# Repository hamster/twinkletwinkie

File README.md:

#TwinkleTwinkie SAO

For fun, I made a twinkling twinkie SAO for my friend @mrtwinkletwink for defcon27.

It is based on an attiny1616, has 3 LEDs and one big capacitive touch button.

 - PDF version is [here](twinkletwinkie.pdf)

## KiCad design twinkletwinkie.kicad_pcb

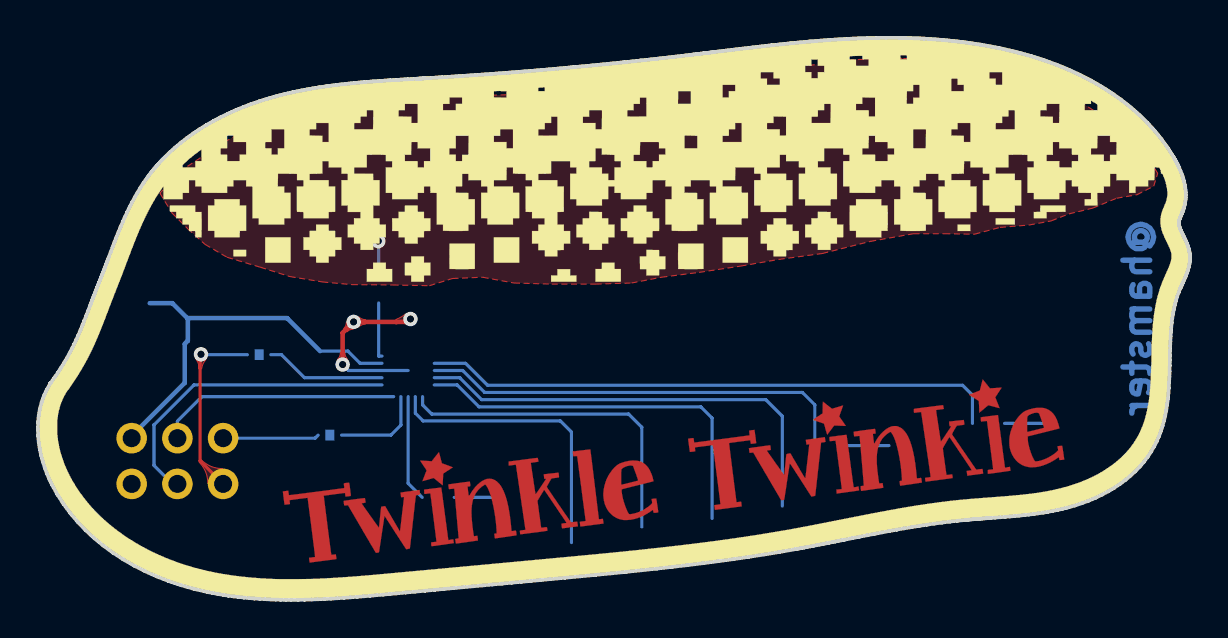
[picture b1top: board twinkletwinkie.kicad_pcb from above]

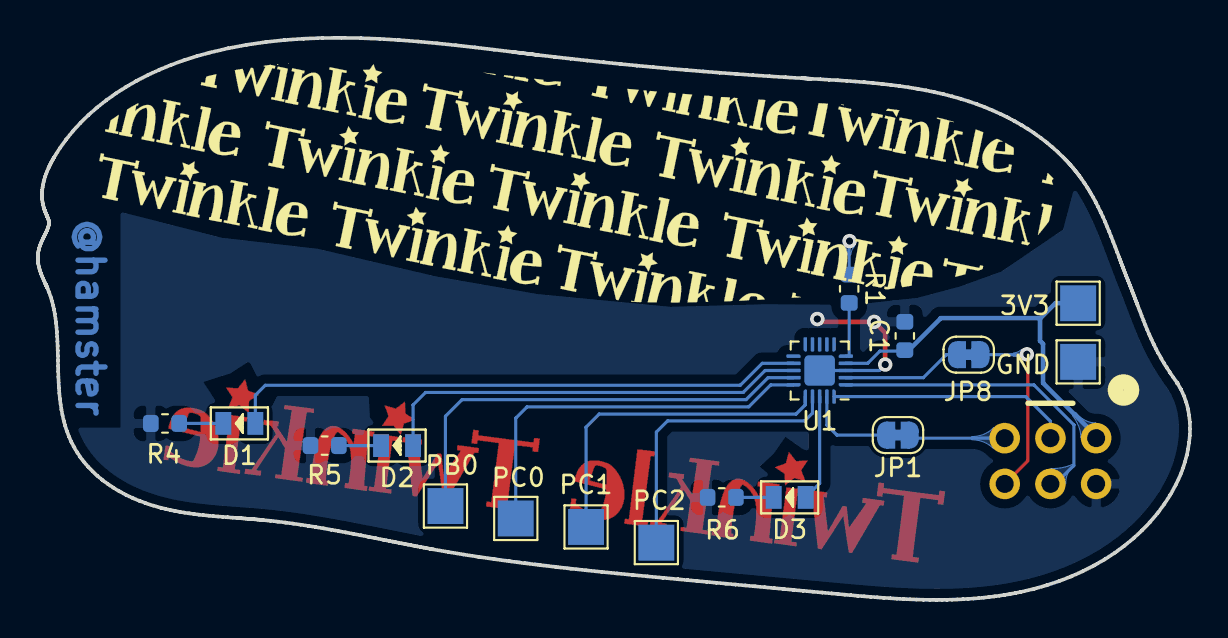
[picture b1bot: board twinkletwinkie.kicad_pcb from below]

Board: 2 copper layers, 64.0 x 31.2 mm, 18 parts (17 on the bottom side), 19 nets.

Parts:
3V3: PB2; TestPoint_Pad_2.0x2.0mm
C1: C; C_0603_1608Metric
D1, D2, D3: LED; LED-0805
GND: PB3; TestPoint_Pad_2.0x2.0mm
JP1, JP8: SolderJumper_2_Bridged; SolderJumper-2_P1.3mm_Bridged_RoundedPad1.0x1.5mm
PB0: PB0; TestPoint_Pad_2.0x2.0mm
PC0: PC0; TestPoint_Pad_2.0x2.0mm
PC1: PC1; TestPoint_Pad_2.0x2.0mm
PC2: PC2; TestPoint_Pad_2.0x2.0mm
R1: 1k; R_0603_1608Metric
R4, R5, R6: 33R; R_0603_1608Metric
U1: ATtiny816-M; VQFN-20-1EP_3x3mm_P0.4mm_EP1.7x1.7mm
X1: Badgelife_sao_connector_v169bis; Badgelife-Shitty-v1.69bis

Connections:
+3V3: 3V3.1, C1.1, U1.4, X1.1
GND: C1.2, GND.1, R4.1, R5.1, R6.1, U1.3, U1.21, X1.2
unnamed: D1.1, R4.2
unnamed: D2.1, R5.2
unnamed: D3.1, R6.2
unnamed: JP1.1, X1.5
unnamed: JP8.2, X1.6
PA0: JP1.2, U1.19
PA1: U1.20, X1.3
PA2: U1.1, X1.4
PA3: JP8.1, U1.2
PA4: R1.2, U1.5
PB0: PB0.1, U1.14
PB1: D2.2, U1.13
PB2: D1.2, U1.12
PC0: PC0.1, U1.15
PC1: PC1.1, U1.16
PC2: PC2.1, U1.17
PC3: D3.2, U1.18

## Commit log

2019-08-23 Adding design files for the TwinkleTwinkie SAO
2019-08-23 Moved schematic image to image directory
